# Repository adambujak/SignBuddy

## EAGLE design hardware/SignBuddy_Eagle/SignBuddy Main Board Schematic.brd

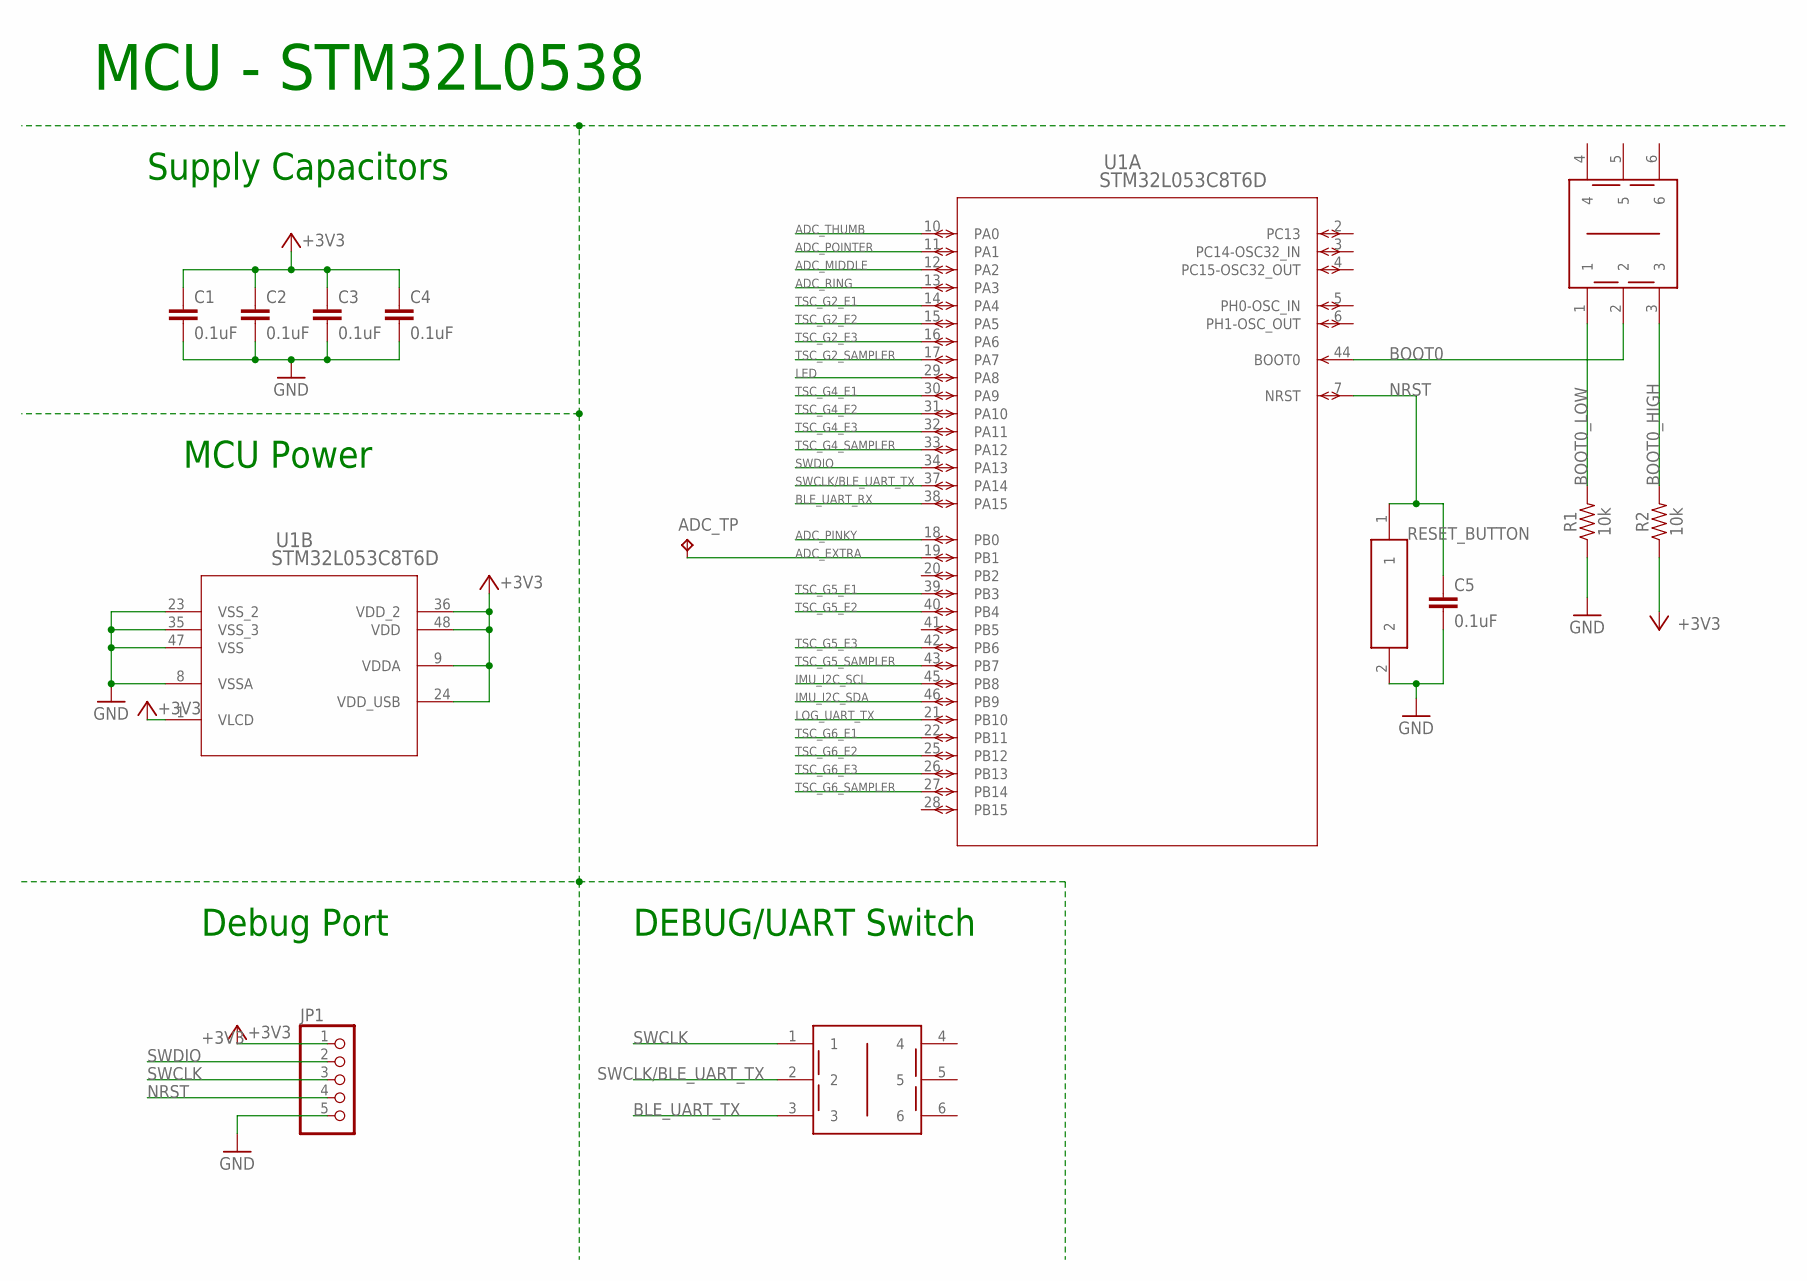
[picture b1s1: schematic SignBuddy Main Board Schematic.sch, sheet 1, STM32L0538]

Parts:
ADC_TP: TPB1,27; B1,27
C1, C2, C3, C4, C5: 0.1uF; 0603
JP1: PINHD-1X5; 1X05
R1, R2: 10k; 0603
RESET_BUTTON: PUSH_BUTTON
U1: STM32L053C8T6D; LQFP48-7X7MM
U$1, U$2: SLIDE_SWITCH

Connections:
+3V3: C1.1, C2.1, C3.1, C4.1, JP1.1, R2.1, U1.1 (VLCD), U1.9 (VDDA), U1.24 (VDD_USB), U1.36 (VDD_2), U1.48 (VDD); also elsewhere on the board
ADC_EXTRA: ADC_TP.TP, U1.19 (PB1)
ADC_MIDDLE: U1.12 (PA2); also elsewhere on the board
ADC_PINKY: U1.18 (PB0); also elsewhere on the board
ADC_POINTER: U1.11 (PA1); also elsewhere on the board
ADC_RING: U1.13 (PA3); also elsewhere on the board
ADC_THUMB: U1.10 (PA0); also elsewhere on the board
BLE_UART_RX: U1.38 (PA15); also elsewhere on the board
BLE_UART_TX: U$2.3; also elsewhere on the board
BOOT0: U1.44 (BOOT0), U$1.2
BOOT0_HIGH: R2.2, U$1.3
BOOT0_LOW: R1.2, U$1.1
GND: C1.2, C2.2, C3.2, C4.2, C5.2, JP1.5, R1.1, RESET_BUTTON.2, U1.8 (VSSA), U1.23 (VSS_2), U1.35 (VSS_3), U1.47 (VSS); also elsewhere on the board
IMU_I2C_SCL: U1.45 (PB8); also elsewhere on the board
IMU_I2C_SDA: U1.46 (PB9); also elsewhere on the board
LED: U1.29 (PA8); also elsewhere on the board
LOG_UART_TX: U1.21 (PB10); also elsewhere on the board
NRST: C5.1, JP1.4, RESET_BUTTON.1, U1.7 (NRST)
SWCLK: JP1.3, U$2.1
SWCLK/BLE_UART_TX: U1.37 (PA14), U$2.2
SWDIO: JP1.2, U1.34 (PA13)
TSC_G2_E1: U1.14 (PA4); also elsewhere on the board
TSC_G2_E2: U1.15 (PA5); also elsewhere on the board
TSC_G2_E3: U1.16 (PA6); also elsewhere on the board
TSC_G2_SAMPLER: U1.17 (PA7); also elsewhere on the board
TSC_G4_E1: U1.30 (PA9); also elsewhere on the board
TSC_G4_E2: U1.31 (PA10); also elsewhere on the board
TSC_G4_E3: U1.32 (PA11); also elsewhere on the board
TSC_G4_SAMPLER: U1.33 (PA12); also elsewhere on the board
TSC_G5_E1: U1.39 (PB3); also elsewhere on the board
TSC_G5_E2: U1.40 (PB4); also elsewhere on the board
TSC_G5_E3: U1.42 (PB6); also elsewhere on the board
TSC_G5_SAMPLER: U1.43 (PB7); also elsewhere on the board
TSC_G6_E1: U1.22 (PB11); also elsewhere on the board
TSC_G6_E2: U1.25 (PB12); also elsewhere on the board
TSC_G6_E3: U1.26 (PB13); also elsewhere on the board
TSC_G6_SAMPLER: U1.27 (PB14); also elsewhere on the board

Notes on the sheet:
MCU - STM32L0538
Supply Capacitors
MCU Power
Debug Port
DEBUG/UART Switch

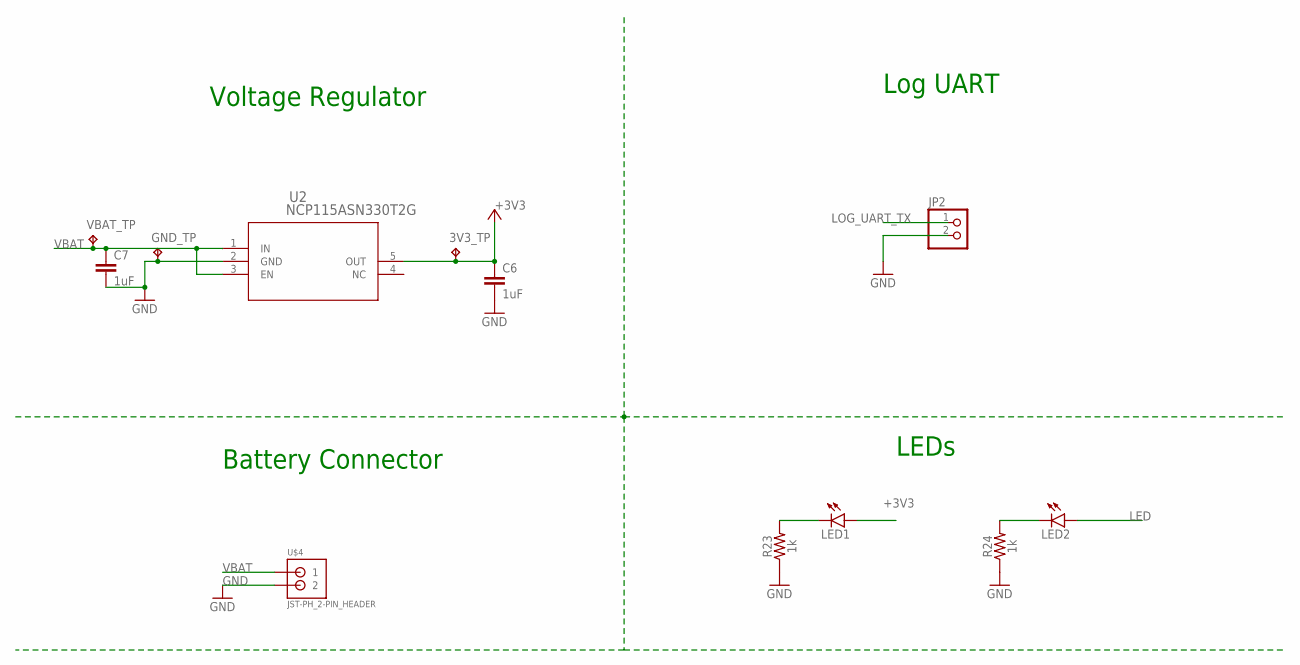
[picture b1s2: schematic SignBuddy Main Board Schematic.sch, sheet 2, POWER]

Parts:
3V3_TP: TPB1,27; B1,27
C6, C7: 1uF; 0603
GND_TP: TPB1,27; B1,27
JP2: PINHD-1X2; 1X02
LED1, LED2: LEDCHIP-LED0603; CHIP-LED0603
R23, R24: 1k; 0603
U2: NCP115ASN330T2G; TSOP-5-483-N_ONS
U$4: JST-PH_2-PIN_HEADER; JST_B2B-PH_HEADER
VBAT_TP: TPB1,27; B1,27

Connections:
+3V3: 3V3_TP.TP, C6.1, LED1.A, U2.5 (OUT); also elsewhere on the board
GND: C6.2, C7.2, GND_TP.TP, JP2.2, R23.1, R24.1, U2.2 (GND), U$4.P2 (2); also elsewhere on the board
LED: LED2.A; also elsewhere on the board
LOG_UART_TX: JP2.1; also elsewhere on the board
unnamed: LED2.C, R24.2
unnamed: LED1.C, R23.2
VBAT: C7.1, U2.1 (IN), U2.3 (EN), U$4.P1 (1), VBAT_TP.TP

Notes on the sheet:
Voltage Regulator
Battery Connector
Log UART
LEDs

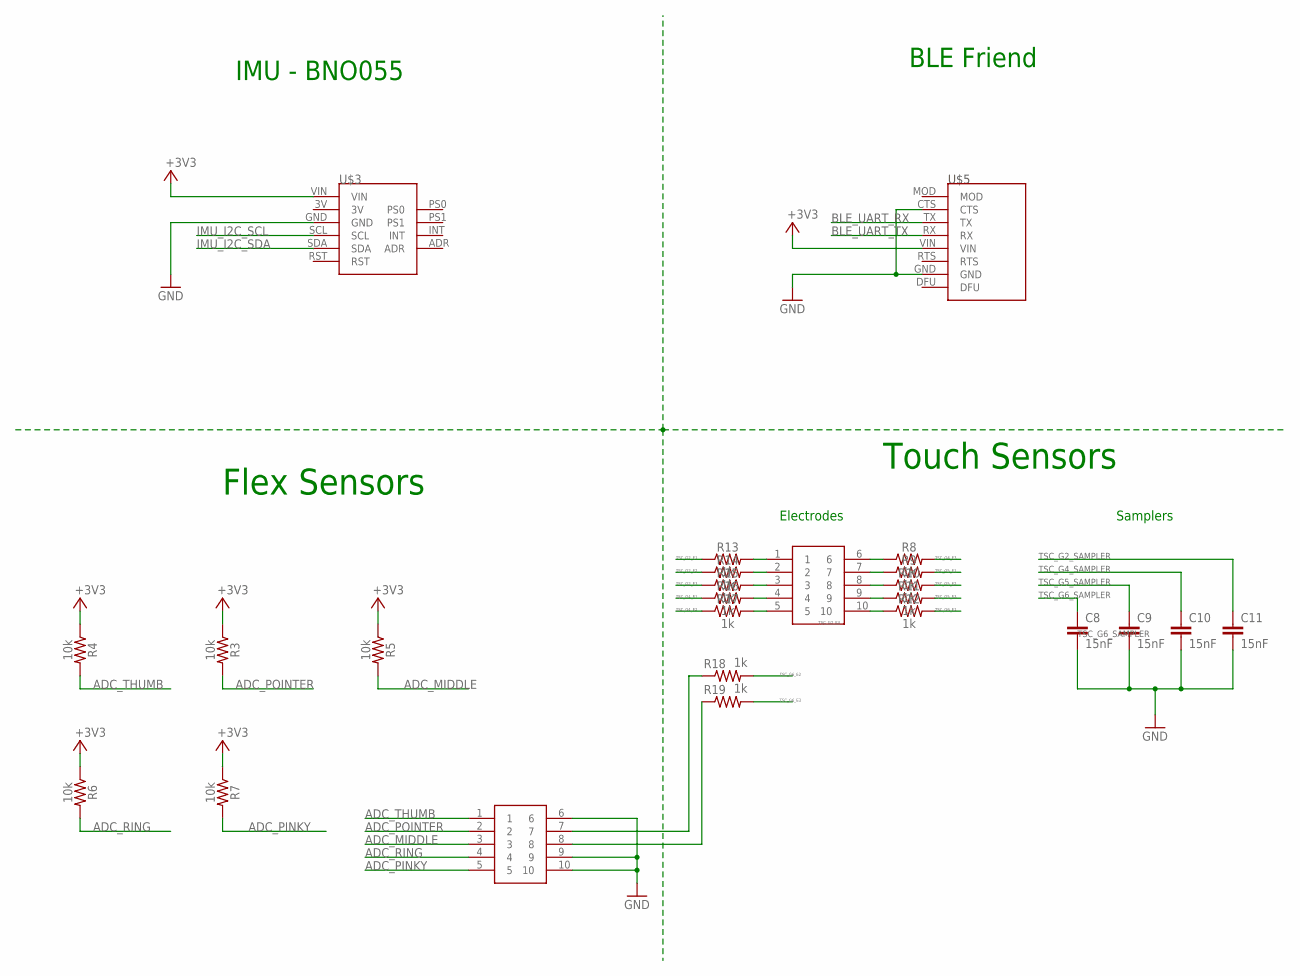
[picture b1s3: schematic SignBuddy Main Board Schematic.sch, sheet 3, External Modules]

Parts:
C8, C9, C10, C11: 15nF; 0603
R3, R4, R5, R6, R7: 10k; 0603
R8, R9, R10, R11, R12, R13, R14, R15, R16, R17, R18, R19: 1k; 0603
U$3: BNO055-ADAFRUIT
U$5: BLE_FRIEND
U$6, U$7: 10PIN_CONNECTOR

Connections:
+3V3: R3.1, R4.1, R5.1, R6.1, R7.1, U$3.VIN, U$5.VIN; also elsewhere on the board
ADC_MIDDLE: R5.2, U$7.3; also elsewhere on the board
ADC_PINKY: R7.2, U$7.5; also elsewhere on the board
ADC_POINTER: R3.2, U$7.2; also elsewhere on the board
ADC_RING: R6.2, U$7.4; also elsewhere on the board
ADC_THUMB: R4.2, U$7.1; also elsewhere on the board
BLE_UART_RX: U$5.TX; also elsewhere on the board
BLE_UART_TX: U$5.RX; also elsewhere on the board
GND: C8.2, C9.2, C10.2, C11.2, U$3.GND, U$5.CTS, U$5.GND, U$7.6, U$7.9, U$7.10; also elsewhere on the board
IMU_I2C_SCL: U$3.SCL; also elsewhere on the board
IMU_I2C_SDA: U$3.SDA; also elsewhere on the board
unnamed: R13.2, U$6.1
unnamed: R18.1, U$7.7
unnamed: R19.1, U$7.8
unnamed: R14.2, U$6.2
unnamed: R15.2, U$6.3
unnamed: R16.2, U$6.4
unnamed: R17.2, U$6.5
unnamed: R8.1, U$6.6
unnamed: R9.1, U$6.7
unnamed: R10.1, U$6.8
unnamed: R11.1, U$6.9
unnamed: R12.1, U$6.10
TSC_G2_E1: R13.1; also elsewhere on the board
TSC_G2_E2: R14.1; also elsewhere on the board
TSC_G2_E3: R15.1; also elsewhere on the board
TSC_G2_SAMPLER: C11.1; also elsewhere on the board
TSC_G4_E1: R16.1; also elsewhere on the board
TSC_G4_E2: R17.1; also elsewhere on the board
TSC_G4_E3: R8.2; also elsewhere on the board
TSC_G4_SAMPLER: C10.1; also elsewhere on the board
TSC_G5_E1: R9.2; also elsewhere on the board
TSC_G5_E2: R10.2; also elsewhere on the board
TSC_G5_E3: R11.2; also elsewhere on the board
TSC_G5_SAMPLER: C9.1; also elsewhere on the board
TSC_G6_E1: R12.2; also elsewhere on the board
TSC_G6_E2: R18.2; also elsewhere on the board
TSC_G6_E3: R19.2; also elsewhere on the board
TSC_G6_SAMPLER: C8.1; also elsewhere on the board

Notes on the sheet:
IMU - BNO055
BLE Friend
Flex Sensors
Touch Sensors
Electrodes
Samplers

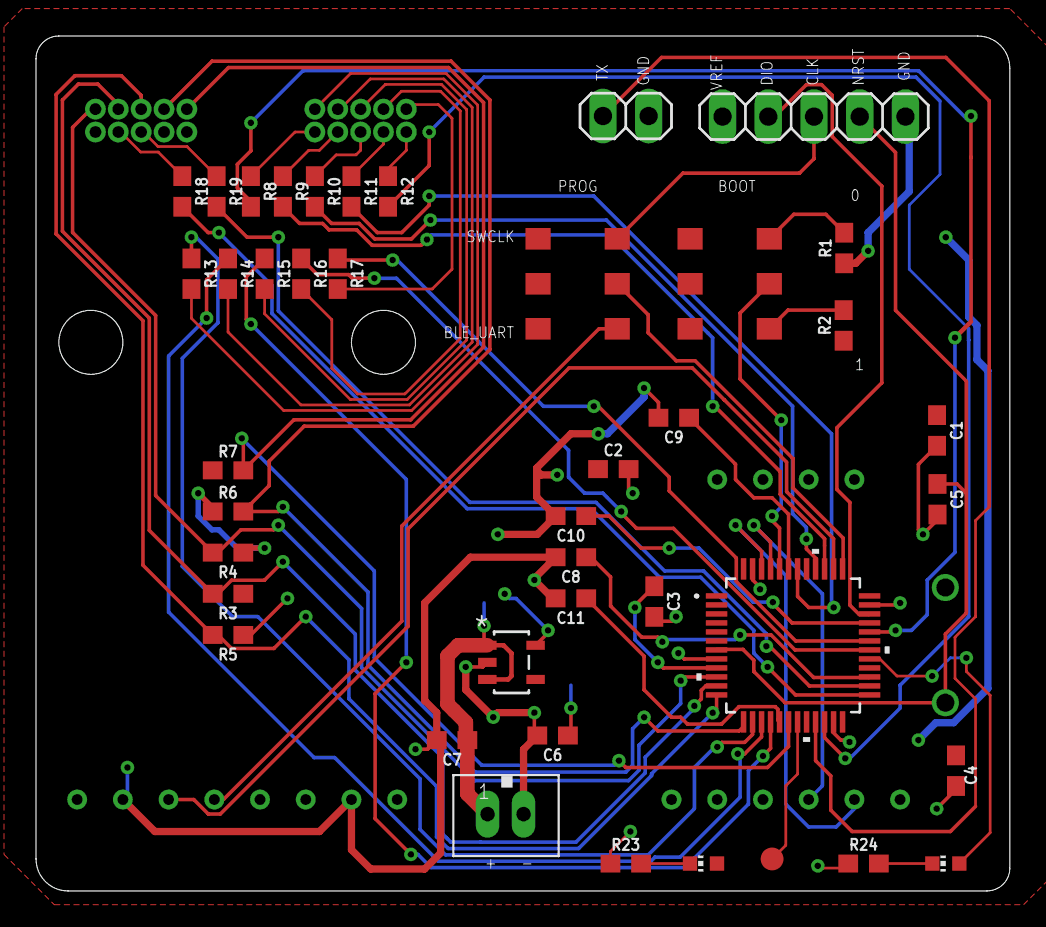
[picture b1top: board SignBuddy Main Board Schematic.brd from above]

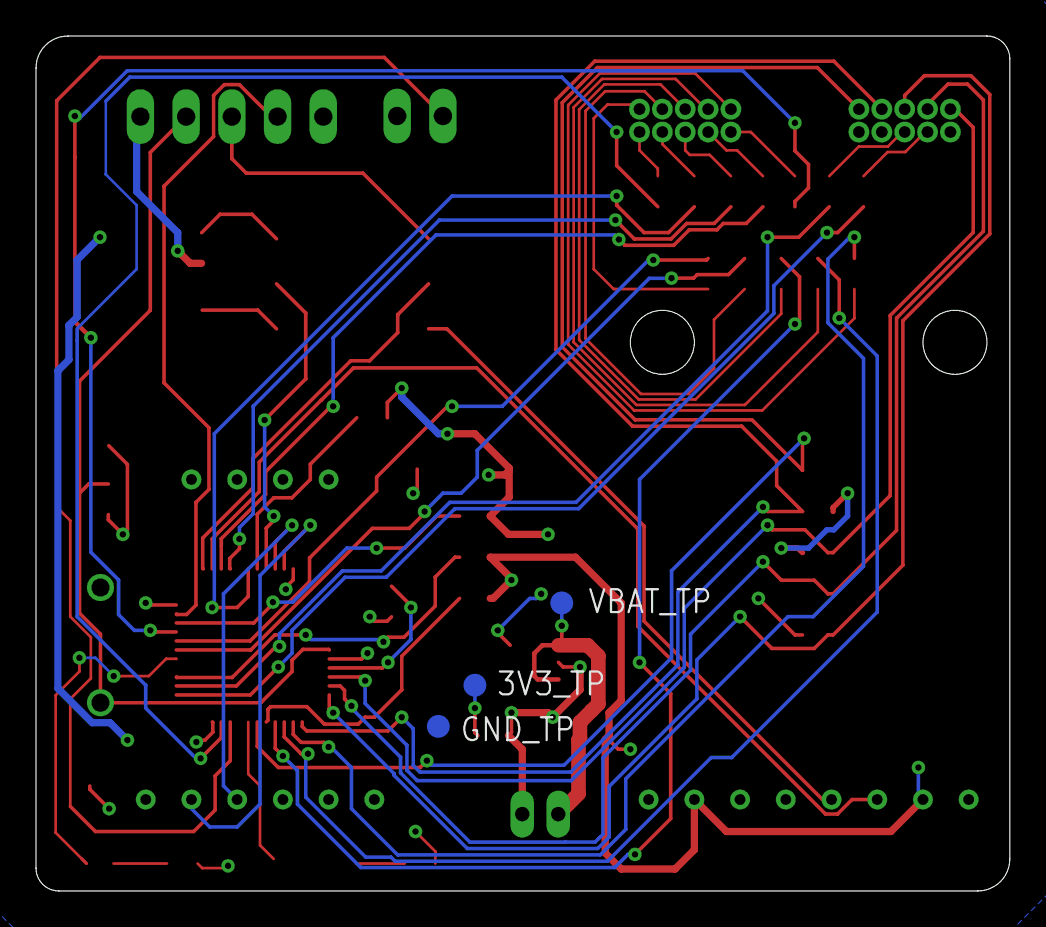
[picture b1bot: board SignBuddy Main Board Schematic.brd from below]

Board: 2 copper layers, 54.1 x 47.5 mm, 50 parts (3 on the bottom side), 52 nets.

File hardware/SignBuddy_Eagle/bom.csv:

"Part";"Value";"Device";"Package";"Description";"COPYRIGHT";"DIGI-KEY_PART_NUMBER_1";"DIGI-KEY_PART_NUMBER_2";"DIGI-KEY_PART_NUMBER_3";"DIGI-KEY_PART_NUMBER_4";"MANUFACTURER_PART_NUMBER";"MFR_NAME";"POPULARITY";"PROD_ID";"TP_SIGNAL_NAME";"VALUE";
"3V3_TP";"TPB1,27";"TPB1,27";"B1,27";"Test pad";"";"";"";"";"";"";"";"19";"";"";"";
"ADC_TP";"TPB1,27";"TPB1,27";"B1,27";"Test pad";"";"";"";"";"";"";"";"19";"";"";"";
"C1";"0.1uF";"10UF-0603-6.3V-20%";"0603";"10.0µF ceramic capacitors";"";"";"";"";"";"";"";"";"CAP-11015";"";"10uF";
"C2";"0.1uF";"10UF-0603-6.3V-20%";"0603";"10.0µF ceramic capacitors";"";"";"";"";"";"";"";"";"CAP-11015";"";"10uF";
"C3";"0.1uF";"10UF-0603-6.3V-20%";"0603";"10.0µF ceramic capacitors";"";"";"";"";"";"";"";"";"CAP-11015";"";"10uF";
"C4";"0.1uF";"10UF-0603-6.3V-20%";"0603";"10.0µF ceramic capacitors";"";"";"";"";"";"";"";"";"CAP-11015";"";"10uF";
"C5";"0.1uF";"10UF-0603-6.3V-20%";"0603";"10.0µF ceramic capacitors";"";"";"";"";"";"";"";"";"CAP-11015";"";"10uF";
"C6";"1uF";"10UF-0603-6.3V-20%";"0603";"10.0µF ceramic capacitors";"";"";"";"";"";"";"";"";"CAP-11015";"";"10uF";
"C7";"1uF";"10UF-0603-6.3V-20%";"0603";"10.0µF ceramic capacitors";"";"";"";"";"";"";"";"";"CAP-11015";"";"10uF";
"C8";"15nF";"10UF-0603-6.3V-20%";"0603";"10.0µF ceramic capacitors";"";"";"";"";"";"";"";"";"CAP-11015";"";"10uF";
"C9";"15nF";"10UF-0603-6.3V-20%";"0603";"10.0µF ceramic capacitors";"";"";"";"";"";"";"";"";"CAP-11015";"";"10uF";
"C10";"15nF";"10UF-0603-6.3V-20%";"0603";"10.0µF ceramic capacitors";"";"";"";"";"";"";"";"";"CAP-11015";"";"10uF";
"C11";"15nF";"10UF-0603-6.3V-20%";"0603";"10.0µF ceramic capacitors";"";"";"";"";"";"";"";"";"CAP-11015";"";"10uF";
"GND_TP";"TPB1,27";"TPB1,27";"B1,27";"Test pad";"";"";"";"";"";"";"";"19";"";"";"";
"JP1";"";"PINHD-1X5";"1X05";"PIN HEADER";"";"";"";"";"";"";"";"69";"";"";"";
"JP2";"";"PINHD-1X2";"1X02";"PIN HEADER";"";"";"";"";"";"";"";"98";"";"";"";
"LED1";"";"LEDCHIP-LED0603";"CHIP-LED0603";"LED";"";"";"";"";"";"";"";"26";"";"";"";
"LED2";"";"LEDCHIP-LED0603";"CHIP-LED0603";"LED";"";"";"";"";"";"";"";"26";"";"";"";
"R1";"10k";"1.8KOHM-0603-1/10W-1%";"0603";"1.8kΩ resistor";"";"";"";"";"";"";"";"";"RES-09119";"";"1.8k";
"R2";"10k";"1.8KOHM-0603-1/10W-1%";"0603";"1.8kΩ resistor";"";"";"";"";"";"";"";"";"RES-09119";"";"1.8k";
"R3";"10k";"10KOHM-0603-1/10W-1%";"0603";"10kΩ resistor";"";"";"";"";"";"";"";"";"RES-00824";"";"10k";
"R4";"10k";"10KOHM-0603-1/10W-1%";"0603";"10kΩ resistor";"";"";"";"";"";"";"";"";"RES-00824";"";"10k";
"R5";"10k";"10KOHM-0603-1/10W-1%";"0603";"10kΩ resistor";"";"";"";"";"";"";"";"";"RES-00824";"";"10k";
"R6";"10k";"10KOHM-0603-1/10W-1%";"0603";"10kΩ resistor";"";"";"";"";"";"";"";"";"RES-00824";"";"10k";
"R7";"10k";"10KOHM-0603-1/10W-1%";"0603";"10kΩ resistor";"";"";"";"";"";"";"";"";"RES-00824";"";"10k";
"R8";"1k";"10KOHM-0603-1/10W-1%";"0603";"10kΩ resistor";"";"";"";"";"";"";"";"";"RES-00824";"";"10k";
"R9";"1k";"10KOHM-0603-1/10W-1%";"0603";"10kΩ resistor";"";"";"";"";"";"";"";"";"RES-00824";"";"10k";
"R10";"1k";"10KOHM-0603-1/10W-1%";"0603";"10kΩ resistor";"";"";"";"";"";"";"";"";"RES-00824";"";"10k";
"R11";"1k";"10KOHM-0603-1/10W-1%";"0603";"10kΩ resistor";"";"";"";"";"";"";"";"";"RES-00824";"";"10k";
"R12";"1k";"10KOHM-0603-1/10W-1%";"0603";"10kΩ resistor";"";"";"";"";"";"";"";"";"RES-00824";"";"10k";
"R13";"1k";"10KOHM-0603-1/10W-1%";"0603";"10kΩ resistor";"";"";"";"";"";"";"";"";"RES-00824";"";"10k";
"R14";"1k";"10KOHM-0603-1/10W-1%";"0603";"10kΩ resistor";"";"";"";"";"";"";"";"";"RES-00824";"";"10k";
"R15";"1k";"10KOHM-0603-1/10W-1%";"0603";"10kΩ resistor";"";"";"";"";"";"";"";"";"RES-00824";"";"10k";
"R16";"1k";"10KOHM-0603-1/10W-1%";"0603";"10kΩ resistor";"";"";"";"";"";"";"";"";"RES-00824";"";"10k";
"R17";"1k";"10KOHM-0603-1/10W-1%";"0603";"10kΩ resistor";"";"";"";"";"";"";"";"";"RES-00824";"";"10k";
"R18";"1k";"10KOHM-0603-1/10W-1%";"0603";"10kΩ resistor";"";"";"";"";"";"";"";"";"RES-00824";"";"10k";
"R19";"1k";"10KOHM-0603-1/10W-1%";"0603";"10kΩ resistor";"";"";"";"";"";"";"";"";"RES-00824";"";"10k";
"R23";"1k";"1.5KOHM-0603-1/10W-1%";"0603";"1.5kΩ resistor";"";"";"";"";"";"";"";"";"RES-08306";"";"1.5k";
"R24";"1k";"1.5KOHM-0603-1/10W-1%";"0603";"1.5kΩ resistor";"";"";"";"";"";"";"";"";"RES-08306";"";"1.5k";
"RESET_BUTTON";"PUSH_BUTTON";"PUSH_BUTTON";"PUSH_BUTTON";"";"";"";"";"";"";"";"";"";"";"";"";
"U$1";"SLIDE_SWITCH";"SLIDE_SWITCH";"SLIDE_SWITCH";"";"";"";"";"";"";"";"";"";"";"";"";
"U$2";"SLIDE_SWITCH";"SLIDE_SWITCH";"SLIDE_SWITCH";"";"";"";"";"";"";"";"";"";"";"";"";
"U$3";"BNO055-ADAFRUIT";"BNO055-ADAFRUIT";"BNO055-ADAFRUIT";"";"";"";"";"";"";"";"";"";"";"";"";
"U$4";"JST-PH_2-PIN_HEADER";"JST-PH_2-PIN_HEADER";"JST_B2B-PH_HEADER";"2-pin JST PH Shrouded Header, top entry";"";"";"";"";"";"";"";"";"";"";"";
"U$5";"BLE_FRIEND";"BLE_FRIEND";"BLE_FRIEND";"";"";"";"";"";"";"";"";"";"";"";"";
"U$6";"10PIN_CONNECTOR";"10PIN_CONNECTOR";"10PIN_CONNECTOR";"";"";"";"";"";"";"";"";"";"";"";"";
"U$7";"10PIN_CONNECTOR";"10PIN_CONNECTOR";"10PIN_CONNECTOR";"";"";"";"";"";"";"";"";"";"";"";"";
"U1";"STM32L053C8T6D";"STM32L053C8T6D";"LQFP48-7X7MM";"";"Copyright (C) 2022 Ultra Librarian. All rights reserved.";"STM32L053C8T6D-ND";"";"";"";"STM32L053C8T6D";"STMicroelectronics";"";"";"";"";
"U2";"NCP115ASN330T2G";"NCP115ASN330T2G";"TSOP-5-483-N_ONS";"";"Copyright (C) 2022 Ultra Librarian. All rights reserved.";"NCP115ASN330T2GOSTR-ND";"NCP115ASN330T2GOSCT-ND";"NCP115ASN330T2GOSDKR-ND";"2156-NCP115ASN330T2G-OS-ND";"NCP115ASN330T2G";"onsemi";"";"";"";"";
"VBAT_TP";"TPB1,27";"TPB1,27";"B1,27";"Test pad";"";"";"";"";"";"";"";"19";"";"";"";

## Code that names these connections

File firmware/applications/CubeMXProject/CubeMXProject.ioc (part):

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Mcu.Name=STM32L053C(6-8)Tx
Mcu.Package=LQFP48
Mcu.UserName=STM32L053C8Tx
PA0.Mode=IN0
PA0.Signal=ADC_IN0
PA1.Mode=IN1
PA1.Signal=ADC_IN1
PA10.Mode=G4_IO2-Channel
PA10.Signal=TSC_G4_IO2
PA11.Mode=G4_IO3-Channel
PA11.Signal=TSC_G4_IO3
PA12.Mode=G4_IO4-Sampling
PA12.Signal=TSC_G4_IO4
PA14.Mode=Asynchronous
PA14.Signal=USART2_TX
PA15.Mode=Asynchronous
PA15.Signal=USART2_RX
PA2.Mode=IN2
PA2.Signal=ADC_IN2
PA3.Mode=IN3
PA3.Signal=ADC_IN3
PA4.Mode=G2_IO1-Channel
PA4.Signal=TSC_G2_IO1
PA5.Mode=G2_IO2-Channel
PA5.Signal=TSC_G2_IO2
PA6.Mode=G2_IO3-Channel
PA6.Signal=TSC_G2_IO3
PA7.Mode=G2_IO4-Sampling
PA7.Signal=TSC_G2_IO4
PA9.Mode=G4_IO1-Channel
PA9.Signal=TSC_G4_IO1
PB0.Mode=IN8
PB0.Signal=ADC_IN8
PB10.Mode=Half_duplex(single_wire_mode)
PB10.Signal=LPUART1_TX
PB11.Mode=G6_IO1-Channel
PB11.Signal=TSC_G6_IO1
PB12.Mode=G6_IO2-Channel
PB12.Signal=TSC_G6_IO2
PB13.Mode=G6_IO3-Channel
PB13.Signal=TSC_G6_IO3
PB14.Mode=G6_IO4-Sampling
PB14.Signal=TSC_G6_IO4
PB3.Mode=G5_IO1-Channel
PB3.Signal=TSC_G5_IO1
PB4.Mode=G5_IO2-Channel
PB4.Signal=TSC_G5_IO2
PB6.Mode=G5_IO3-Channel
PB6.Signal=TSC_G5_IO3
PB7.Mode=G5_IO4-Sampling
PB7.Signal=TSC_G5_IO4
PB8.Mode=I2C
PB8.Signal=I2C1_SCL
PB9.Mode=I2C
PB9.Signal=I2C1_SDA
RCC.HSE_VALUE=8000000
RCC.SYSCLKFreq_VALUE=24000000
RCC.SYSCLKSource=RCC_SYSCLKSOURCE_PLLCLK
board=custom

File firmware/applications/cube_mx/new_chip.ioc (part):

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Mcu.Name=STM32L053R(6-8)Tx
Mcu.Package=LQFP64
Mcu.UserName=STM32L053R8Tx
PA0.Mode=IN0
PA0.Signal=ADC_IN0
PA1.Mode=IN1
PA1.Signal=ADC_IN1
PA10.Mode=G4_IO2-Channel
PA10.Signal=TSC_G4_IO2
PA12.Mode=G4_IO4-Sampling
PA12.Signal=TSC_G4_IO4
PA13.Mode=Serial_Wire
PA13.Signal=SYS_SWDIO
PA14.Mode=Serial_Wire
PA14.Signal=SYS_SWCLK
PA15.Signal=S_TIM2_ETR
PA2.GPIOParameters=GPIO_Label
PA2.GPIO_Label=USART_TX
PA2.Mode=Synchronous
PA2.Signal=USART2_TX
PA3.GPIOParameters=GPIO_Label
PA3.GPIO_Label=USART_RX
PA3.Mode=Synchronous
PA3.Signal=USART2_RX
PA4.Mode=Synchronous
PA4.Signal=USART2_CK
PA5.GPIOParameters=GPIO_Label
PA5.GPIO_Label=LD2 [Green Led]
PA5.Signal=GPIO_Output
PA6.Mode=IN6
PA6.Signal=ADC_IN6
PA7.Mode=IN7
PA7.Signal=ADC_IN7
PA9.Mode=G4_IO1-Channel
PA9.Signal=TSC_G4_IO1
PB0.Mode=IN8
PB0.Signal=ADC_IN8
PB1.Mode=G3_IO3-Channel
PB1.Signal=TSC_G3_IO3
PB11.Mode=G6_IO1-Channel
PB11.Signal=TSC_G6_IO1
PB12.Mode=G6_IO2-Channel
PB12.Signal=TSC_G6_IO2
PB14.Mode=G6_IO4-Sampling
PB14.Signal=TSC_G6_IO4
PB2.Mode=G3_IO4-Sampling
PB2.Signal=TSC_G3_IO4
PB3.Mode=G5_IO1-Channel
PB3.Signal=TSC_G5_IO1
PB4.Mode=G5_IO2-Channel
PB4.Signal=TSC_G5_IO2
PB6.Mode=I2C
PB6.Signal=I2C1_SCL
PB7.Mode=G5_IO4-Sampling
PB7.Signal=TSC_G5_IO4
PB9.Mode=I2C
PB9.Signal=I2C1_SDA
PC0.Mode=G7_IO1-Channel
PC0.Signal=TSC_G7_IO1
PC1.Mode=G7_IO2-Channel
PC1.Signal=TSC_G7_IO2
PC10.Mode=Asynchronous
PC10.Signal=LPUART1_TX
PC11.Mode=Asynchronous
PC11.Signal=LPUART1_RX
PC3.Mode=G7_IO4-Sampling
PC3.Signal=TSC_G7_IO4
PC5.Mode=G3_IO1-Channel
PC5.Signal=TSC_G3_IO1
PC6.Mode=G8_IO1-Channel
PC6.Signal=TSC_G8_IO1
PC7.Mode=G8_IO2-Channel
PC7.Signal=TSC_G8_IO2
PC9.Mode=G8_IO4-Sampling
PC9.Signal=TSC_G8_IO4
PH0-OSC_IN.Mode=HSE-External-Clock-Source
PH0-OSC_IN.Signal=RCC_OSC_IN
RCC.HSE_VALUE=8000000
RCC.SYSCLKFreq_VALUE=24000000
RCC.SYSCLKSource=RCC_SYSCLKSOURCE_PLLCLK
board=NUCLEO-L053R8
boardIOC=true

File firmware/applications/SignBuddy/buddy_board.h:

#ifndef BUDDY_BOARD_H
#define BUDDY_BOARD_H

#include "stm32l0xx_ll_adc.h"
#include "stm32l0xx_ll_bus.h"
#include "stm32l0xx_ll_cortex.h"
#include "stm32l0xx_ll_crc.h"
#include "stm32l0xx_ll_dma.h"
#include "stm32l0xx_ll_exti.h"
#include "stm32l0xx_ll_gpio.h"
#include "stm32l0xx_ll_i2c.h"
#include "stm32l0xx_ll_lpuart.h"
#include "stm32l0xx_ll_pwr.h"
#include "stm32l0xx_ll_rcc.h"
#include "stm32l0xx_ll_system.h"
#include "stm32l0xx_ll_tim.h"
#include "stm32l0xx_ll_usart.h"
#include "stm32l0xx_ll_utils.h"
#include "stm32l0xx_hal.h"

#define SYSCLK_FREQ               24000000

/* LED */
#define LED1_PORT                 GPIOA
#define LED1_PIN                  LL_GPIO_PIN_8
#define GPIO_LED_CLK_EN()         LL_IOP_GRP1_EnableClock(LL_IOP_GRP1_PERIPH_GPIOA)

/* BLE UART */
#define BLE_UART                  USART2
#define BLE_UART_GPIO_PORT        GPIOA
#define BLE_UART_TX_PIN           LL_GPIO_PIN_14
#define BLE_UART_RX_PIN           LL_GPIO_PIN_15
#define BLE_UART_GPIO_AF          LL_GPIO_AF_4
#define BLE_UART_RXNE()           LL_USART_IsActiveFlag_RXNE(USART2)
#define BLE_UART_TXE()            LL_USART_IsActiveFlag_TXE(USART2)
#define BLE_UART_CLK_SRC()        LL_RCC_SetUSARTClockSource(LL_RCC_USART2_CLKSOURCE_PCLK1)
#define BLE_UART_CLK_EN()         LL_APB1_GRP1_EnableClock(LL_APB1_GRP1_PERIPH_USART2)
#define BLE_UART_GPIO_CLK_EN()    LL_IOP_GRP1_EnableClock(LL_IOP_GRP1_PERIPH_GPIOA)


/* LOG UART */
#define LOG_UART                    LPUART1
#define LOG_UART_GPIO_PORT          GPIOB
#define LOG_UART_TX_PIN             LL_GPIO_PIN_10
#define LOG_UART_GPIO_AF            LL_GPIO_AF_4
#define LOG_UART_BAUDRATE           115200
#define LOG_UART_CLK_SRC()          LL_RCC_SetLPUARTClockSource(LL_RCC_LPUART1_CLKSOURCE_PCLK1)
#define LOG_UART_CLK_EN()           LL_APB1_GRP1_EnableClock(LL_APB1_GRP1_PERIPH_LPUART1)
#define LOG_UART_GPIO_CLK_EN()      LL_IOP_GRP1_EnableClock(LL_IOP_GRP1_PERIPH_GPIOB)

/* FLEX */
#define FLEX_THUMB_PORT             GPIOA
#define FLEX_THUMB_PIN              LL_GPIO_PIN_0
#define FLEX_THUMB_CHANNEL          LL_ADC_CHANNEL_0
#define FLEX_INDEX_PORT             GPIOA
#define FLEX_INDEX_PIN              LL_GPIO_PIN_1
#define FLEX_INDEX_CHANNEL          LL_ADC_CHANNEL_1
#define FLEX_MIDDLE_PORT            GPIOA
#define FLEX_MIDDLE_PIN             LL_GPIO_PIN_2
#define FLEX_MIDDLE_CHANNEL         LL_ADC_CHANNEL_2
#define FLEX_RING_PORT              GPIOA
#define FLEX_RING_PIN               LL_GPIO_PIN_3
#define FLEX_RING_CHANNEL           LL_ADC_CHANNEL_3
#define FLEX_LITTLE_PORT            GPIOB
#define FLEX_LITTLE_PIN             LL_GPIO_PIN_0
#define FLEX_LITTLE_CHANNEL         LL_ADC_CHANNEL_8
#define FLEX_GPIO_CLK_EN()          LL_IOP_GRP1_EnableClock(LL_IOP_GRP1_PERIPH_GPIOA); \
  LL_IOP_GRP1_EnableClock(LL_IOP_GRP1_PERIPH_GPIOB);

/* I2C */
#define IMU_I2C                     I2C1
#define IMU_I2C_SCL_PIN             LL_GPIO_PIN_8
#define IMU_I2C_SDA_PIN             LL_GPIO_PIN_9
#define IMU_I2C_GPIO_AF             LL_GPIO_AF_4
#define IMU_I2C_GPIO_PORT           GPIOB
#define IMU_I2C_CLK_SRC()           LL_RCC_SetI2CClockSource(LL_RCC_I2C1_CLKSOURCE_PCLK1);
#define IMU_I2C_CLK_EN()            LL_IOP_GRP1_EnableClock(LL_IOP_GRP1_PERIPH_GPIOB);
#define IMU_I2C_GPIO_CLK_EN()       LL_APB1_GRP1_EnableClock(LL_APB1_GRP1_PERIPH_I2C1);

/* TSC */
#define TSC_ELECTRODE_AF            LL_GPIO_AF_3
#define TSC_SAMPLER_AF              LL_GPIO_AF_3

// GROUP 2
#define TSC_GROUP2_CHANNEL0_PORT    GPIOA
#define TSC_GROUP2_CHANNEL0_PIN     LL_GPIO_PIN_4
#define TSC_GROUP2_CHANNEL0_IO      TSC_GROUP2_IO1

#define TSC_GROUP2_CHANNEL1_PORT    GPIOA
#define TSC_GROUP2_CHANNEL1_PIN     LL_GPIO_PIN_5
#define TSC_GROUP2_CHANNEL1_IO      TSC_GROUP2_IO2

#define TSC_GROUP2_CHANNEL2_PORT    GPIOA
#define TSC_GROUP2_CHANNEL2_PIN     LL_GPIO_PIN_6
#define TSC_GROUP2_CHANNEL2_IO      TSC_GROUP2_IO3

#define TSC_GROUP2_SAMPLER_PORT     GPIOA
#define TSC_GROUP2_SAMPLER_PIN      LL_GPIO_PIN_7
#define TSC_GROUP2_SAMPLER_IO       TSC_GROUP2_IO4

// GROUP 4
#define TSC_GROUP4_CHANNEL0_PORT    GPIOA
#define TSC_GROUP4_CHANNEL0_PIN     LL_GPIO_PIN_9
#define TSC_GROUP4_CHANNEL0_IO      TSC_GROUP4_IO1

#define TSC_GROUP4_CHANNEL1_PORT    GPIOA
#define TSC_GROUP4_CHANNEL1_PIN     LL_GPIO_PIN_10
#define TSC_GROUP4_CHANNEL1_IO      TSC_GROUP4_IO2

#define TSC_GROUP4_CHANNEL2_PORT    GPIOA
#define TSC_GROUP4_CHANNEL2_PIN     LL_GPIO_PIN_11
#define TSC_GROUP4_CHANNEL2_IO      TSC_GROUP4_IO3

#define TSC_GROUP4_SAMPLER_PORT     GPIOA
#define TSC_GROUP4_SAMPLER_PIN      LL_GPIO_PIN_12
#define TSC_GROUP4_SAMPLER_IO       TSC_GROUP4_IO4

// GROUP 5
#define TSC_GROUP5_CHANNEL0_PORT    GPIOB
#define TSC_GROUP5_CHANNEL0_PIN     LL_GPIO_PIN_3
#define TSC_GROUP5_CHANNEL0_IO      TSC_GROUP5_IO1

#define TSC_GROUP5_CHANNEL1_PORT    GPIOB
#define TSC_GROUP5_CHANNEL1_PIN     LL_GPIO_PIN_4
#define TSC_GROUP5_CHANNEL1_IO      TSC_GROUP5_IO2

#define TSC_GROUP5_CHANNEL2_PORT    GPIOB
#define TSC_GROUP5_CHANNEL2_PIN     LL_GPIO_PIN_6
#define TSC_GROUP5_CHANNEL2_IO      TSC_GROUP5_IO3

#define TSC_GROUP5_SAMPLER_PORT     GPIOB
#define TSC_GROUP5_SAMPLER_PIN      LL_GPIO_PIN_7
#define TSC_GROUP5_SAMPLER_IO       TSC_GROUP5_IO4

// GROUP 6
#define TSC_GROUP6_CHANNEL0_PORT    GPIOB
#define TSC_GROUP6_CHANNEL0_PIN     LL_GPIO_PIN_11
#define TSC_GROUP6_CHANNEL0_IO      TSC_GROUP6_IO1

#define TSC_GROUP6_CHANNEL1_PORT    GPIOB
#define TSC_GROUP6_CHANNEL1_PIN     LL_GPIO_PIN_12
#define TSC_GROUP6_CHANNEL1_IO      TSC_GROUP6_IO2

#define TSC_GROUP6_CHANNEL2_PORT    GPIOB
#define TSC_GROUP6_CHANNEL2_PIN     LL_GPIO_PIN_13
#define TSC_GROUP6_CHANNEL2_IO      TSC_GROUP6_IO3

#define TSC_GROUP6_SAMPLER_PORT     GPIOB
#define TSC_GROUP6_SAMPLER_PIN      LL_GPIO_PIN_14
#define TSC_GROUP6_SAMPLER_IO       TSC_GROUP6_IO4


#define TSC_CLK_EN()                LL_AHB1_GRP1_EnableClock(LL_AHB1_GRP1_PERIPH_TSC)
#define TSC_GPIO_CLK_EN()           LL_IOP_GRP1_EnableClock(LL_IOP_GRP1_PERIPH_GPIOA); \
  LL_IOP_GRP1_EnableClock(LL_IOP_GRP1_PERIPH_GPIOB);                                   \

#endif // BUDDY_BOARD_H

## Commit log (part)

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2021-11-18 change default make target
2021-11-18 change adc naming
2021-11-18 Add STM32L0 Cube library (#37)
2021-11-18 Revamp formatter script - Separate into docker and non docker script - Add blacklist file
2021-11-18 change makefile to use docker format script
2021-11-18 change gitattributes
2021-11-18 fix error handler
2021-11-18 remove error_handler
2021-11-18 lpuart sending data
2021-11-18 Revamp formatter script (#40)
    * Revamp formatter script
    - Separate into docker and non docker script
    - Add blacklist file
    * change makefile to use docker format script
    * remove line ending gitattribute
    * change gitattributes
2021-11-18 fix system timer issue
2021-11-18 Support for nucleo L0
2021-11-18 Update workflow for Nucleo L0
2021-11-18 run formatter
2021-11-18 Add support for L0, remove L4 support (#42)
    * Modify makefile for nucleo l0
    * Support for nucleo L0
    * Update workflow for Nucleo L0
    * fix system timer issue
    * delete all l4 code
    * run formatter
2021-11-18 add test run script
2021-11-18 add test framework
2021-11-18 add tests to makefile
2021-11-18 fix echoerr
2021-11-18 fix drop bug
2021-11-18 add test_runnners directory to gitignore
2021-11-18 add drop tests
2021-11-18 change calling of docker build
2021-11-18 Make test fail to test if github test fails
2021-11-18 fix fifo and add test framework (#36)
    * fix fifo
    * add test framework
    * add test run script
    * add tests to makefile
    * add test_runnners directory to gitignore
    * Add testing to github
2021-11-19 Formatting
2021-11-19 fix docker scripts (#45)
    * fix docker scripts
    * Formatting
2021-11-19 add max line width
2021-11-19 Removed stm32l4 references
2021-11-19 make references use system's default line endings (#47)
2021-11-19 Removed stm32l4 references (#48)
2021-11-19 add jlink flash
2021-11-19 add jlink flash support (#49)
    * add jlink flash
    * add flash_jlink to main makefile
2021-11-19 Add initial KiCad project for hw design
2021-11-20 Cleanup board header
2021-11-20 Switch stm32l0 source to STM repo
2021-11-20 Cleanup board header (#61)
    * Cleanup board header
    * Add back in log uart baud macro
2021-11-20 Switch stm32l0 source to STM repo (#62)
2021-11-20 Created KiCad project and added main components (#60)
    * Add initial KiCad project for hw design
    * Add nrf and bno
2021-11-20 add imu module
2021-11-21 add space after cast
2021-11-22 fixup github actions config
2021-11-22 fixup github actions config (#66)
2021-11-22 work on bno0555
2021-11-22 dev_addr changed
2021-11-22 increase i2c speed
2021-11-22 changed parameter based on i2c module
2021-11-22 updated imu_process
2021-11-22 moved bno_struct under state struct
2021-11-22 prints AMG_xyz data
2021-11-22 change write/read in i2c module
2021-11-22 formatted
2021-11-22 abstracted and modified imu
2021-11-22 Modify workflow
2021-11-22 test if fail stops everything else
2021-11-22 add imu module (#64)
    * add bno library
    * add imu module
    * add imu module
    * work on bno0555
    * dev_addr changed
    * make i2c work
2021-11-22 Action test
2021-11-22 add nucleo user manual
2021-11-22 add nucleo user manual (#69)
2021-11-23 test2'
2021-11-23 Modify workflow (#67)
    * Modify workflow
    * Add always statements to ensure tests run post failure
2022-01-13 Updated Home screen
2022-01-14 Lesson Pages
    Added lesson activity and integrated with main
2022-01-15 Changed BLE folder path
2022-01-15 Bluetooth
2022-01-15 Welcome Message
2022-01-28 Add on-click listener for connect button
2022-01-28 Removed bluefruit folder
2022-01-29 Update dependencies
2022-01-29 add tsc
2022-01-30 Fix corrupt logo
2022-02-01 Add in BLE support on the Android app (#74)
    * Add on-click listener for connect button
    * Removed bluefruit folder
    * Add FastBle dependency
    * Update dependencies
    * Added bluetooth functionality
    * Fix corrupt logo
2022-02-02 Add example protobuf generation
2022-02-03 quat data
2022-02-03 format
2022-02-03 add freertos kernel
2022-02-03 touch sense integration (#75)
    * touch sense working
    * format
    * format
    * fix
    * add freertos kernel
2022-02-03 Reading Quaternion data (#78)
    * quat data
    * moved operation mode function out of get_data()
    * format
2022-02-03 Moved proto build to higher level makefile
2022-02-03 Fix typo
2022-02-03 added calibration status
2022-02-03 added cube mx generated project
2022-02-03 remove file
2022-02-04 fix formatting blacklist
2022-02-04 fix formatting blacklist (#83)
2022-02-04 integrate freertos
2022-02-04 Add error handling for I2C
2022-02-04 Switch to signed int
2022-02-04 fix assert_param warnings
2022-02-04 reduce ble_buffer size
2022-02-04 fix assert_param warnings (#86)
    * fix assert_param warnings
    * format
2022-02-04 reduce logger buffer sizes (#85)
2022-02-04 quick fixes
2022-02-04 changing tsc module to rtos scheme (#82)
    * tsc rearchitecture
2022-02-04 Revert "changing tsc module to rtos scheme (#82)"
    This reverts commit 91d570239b4162a52882f424bc160bf6ccf484d5.
2022-02-04 integrate tsc rtos module
2022-02-04 integrate tsc rtos module (#89)
2022-02-04 fix if
2022-02-05 Add sampling timer
2022-02-05 Fix error from merge with timer branch
2022-02-05 Fix priorities
2022-02-05 Add packet structure
2022-02-05 Add sample packet to sensors module, add timer stop
2022-02-05 add tsc calibration feature (#91)
    * add tsc calibration and improve reliability
    * fix if
2022-02-07 add touch sensor and programming lines (#99)
2022-02-07 Move cubemx file to hardware directory
2022-02-07 Rename sign buddy logo
2022-02-07 Initial Android software with BLE functionality (#90)
    * Create menu_neopixel.xml
    * Added Connect button
    * Updated Home screen
    * Lesson Pages
    * Adding BLE module
    * Main Screen formatting
2022-02-07 Add comms task and packet encoding
2022-02-07 Remove blocking from comms, simplify data transaction
2022-02-07 Encoded length is debug msg
2022-02-07 Add crc on encoded packet
2022-02-07 Simplify implementation
2022-02-07 Increase tx buffer
2022-02-07 Remove include
2022-02-07 Add commented semaphore, program is crashing when uncommented
2022-02-07 Add mutex on sample data
2022-02-07 Comment mutex handle
2022-02-07 Make flags volatile
2022-02-07 Remove unused process period
2022-02-07 Change lpuart baud rate and sensor sampling period
2022-02-07 Add command to start sampling
2022-02-07 Remove unnecessary pointer
2022-02-07 Rename mid for clarity
2022-02-07 Move size check inside ingest_packet
2022-02-07 make crc work
2022-02-07 Add comms task (#97)
    * Add comms task and packet encoding
    * Get encoded packet length
    * Remove blocking from comms, simplify data transaction
    * Encoded length is debug msg
    * Add crc on encoded packet
    * Remove DMA
2022-02-07 Fix crc function call
2022-02-08 fix sampling timer
2022-02-08 fix sampling timer (#105)
2022-02-08 add support for multiple channels and multiple groups
    run formatter
2022-02-08 define all tsc pins
2022-02-08 improve sensors data collection
    format
    revert proto
    add log back
2022-02-08 consolidate tsc value getters
2022-02-08 move tsc init to hw_init
2022-02-08 fix ble pins AF
2022-02-08 Fix ble uart alternate function
2022-02-08 Move message id into protobuf and add status message (#104)
    * Move msg id into protobuf
    * Fix crc function call
2022-02-08 adding support for multiple tsc sensors (#92)
    * define all tsc pins
    * add support for multiple channels and multiple groups
    run formatter
    * improve sensors data collection
    format
    revert proto
2022-02-08 downsize logger
2022-02-08 remove system time module (#110)
    * remove system time module
    * run formatter
2022-02-08 imu_task changes
2022-02-08 remove log read
2022-02-08 downsize logger (#111)
    * downsize logger
    * remove log read
2022-02-09 Added IMU Task using freeRTOS (#98)
    * imu_task changes
    * remove led task
    * generate proto and rename fields
2022-02-09 Change flex get data
2022-02-09 Change flex get data (#113)
    * Change flex get data
    * Add flex sensor indices
2022-02-09 move irq priorities, and delete unused ones
2022-02-09 move irq priorities, and delete unused ones (#114)
2022-02-09 Fix flex index (#115)
2022-02-09 reduced touch values to one uint16
2022-02-09 change imu pins
2022-02-09 change imu pins (#116)
2022-02-09 Change BLE name and log hex values
2022-02-09 add all 12 touch sensors
2022-02-09 add all touch sensors (#112)
    * add all 12 touch sensors
    * run formatter
2022-02-09 remove tsc log
2022-02-09 new cube project
2022-02-09 Switch proto naming convention
2022-02-09 Switch proto naming convention (#119)
2022-02-10 working slightly
2022-02-10 cleanup
2022-02-10 fix comment error
2022-02-10 update lpuart calls in comms
2022-02-11 schematic done
2022-02-11 board done
2022-02-12 Add status led and adc test point
2022-02-12 Add status led and adc test point (#124)
    * Add status led and adc test point
    * fixes
2022-02-12 fixups
2022-02-12 add pcb and schematic (#125)
    * initial commit
    * schematic done
    * board done
    * fixes
    * Add status led and adc test point
    * fixes
2022-02-13 small route fix
2022-02-13 add gitignore
2022-02-15 pcb finalization (#126)
    * small route fix
    * add bom
    * add gitignore
    * delete unneccessary files
2022-02-15 add pcb screenshots and gerber (#127)
2022-02-15 add gittattributes
2022-02-17 Add lock on potentially shared data
2022-02-17 Add Sign Buddy proto file and protobuf module
2022-02-17 Add protobuf parsing functionality
2022-02-17 Added gesture builder
2022-02-17 Update gradle
2022-02-17 Save training data to file
2022-02-19 Add command to sample once
2022-02-20 Capitalize constants, clarify sampling once vs periodic
2022-02-20 Add protobuf to app and training data collection (#129)
    * Update gradle
    * Update dependencies
    * Add Sign Buddy proto file and protobuf module
    * Formatting proto
    * Replace with updated proto
    * Add protobuf parsing functionality
2022-02-22 Add enum for static/dynamic sampling
2022-02-22 add buddy board support
2022-02-22 remove error and add expansion diagram
2022-02-22 add tests to github
2022-02-22 add buddy board support (#140)
    * add buddy board support
    * remove error and add expansion diagram
    * add tests to github
2022-02-22 working
2022-02-22 move
2022-02-23 remove format step from build_proto
2022-02-23 add delay to start of application
2022-02-23 add delay to start of application (#144)
2022-02-23 Add protoc dependency in docker image
2022-02-23 move android app to subdirectory
2022-02-23 update android build test
2022-02-23 add sidekick app
2022-02-23 Remove .idea
2022-02-23 Remove .idea (#146)
2022-02-23 added decoder, crc wrong
2022-02-23 Compile proto for javalite at higher level
2022-02-23 Add software readme placeholder
2022-02-23 reading in data
2022-02-24 added sampling commands
2022-02-24 changed to relative and quaternion
2022-03-03 Pulled from Master
2022-03-07 Adding Sign Pictures
2022-03-14 Lesson Activity
2022-03-19 Remove linear accelartion, update java proto
2022-03-19 Hs/rel quat (#149)
    * changed to relative and quaternion
    * format
    * Remove linear accelartion, update java proto
    * Formatting
2022-03-22 Reset offsets
2022-03-22 Add IMU reset cmd to app
2022-03-23 Calibrate flex sensors
2022-03-23 Calibrate flex sensors (#151)
2022-03-23 Add IMU calib status check
2022-03-31 add sidekick application (#143)
    * add sidekick app
    * added decoder, crc wrong
    * reading in data
    * ran formatter
    * added sampling commands
2022-03-31 Add initial model creation
2022-03-31 Fix normalization and change model
2022-03-31 Save norms
2022-03-31 Perform training/test normalization separately
2022-03-31 Remove top level python file
2022-03-31 Add trained SVM model (#153)
    * Add initial model creation
    * Add confusion matrix visualization
    * Fix normalization and change model
    * Save norms
    * Rename classification script
    * Perform training/test normalization separately
2022-04-01 Adding Quiz mode
2022-04-01 Update qBjuwb8Fz9Ld9bb0YORqfh1HpEc=
2022-04-04 Export model to java
2022-04-04 Add SVC to android app
2022-04-04 Update SVC to account for bug
2022-04-04 Add classifier to Android app (#157)
    * Export model to java
    * Add SVC to android app
    * Fix parsing bug
    * Update SVC to account for bug
2022-04-04 deleted unnecessary files
2022-04-11 Force light mode
2022-04-12 Change SVCalpha

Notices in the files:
parts and their libraries:
SparkFun-Capacitors: Licensing: Creative Commons ShareAlike 4.0 International - https://creativecommons.org/licenses/by-sa/4.0
COPYRIGHT: Copyright (C) 2022 Ultra Librarian. All rights reserved.
